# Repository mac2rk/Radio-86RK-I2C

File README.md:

# I2C interface for i8080 (and simlilar) computers

(The wire fixes an error in an intial version of the board; in the Eagle and Gerber files available here the error has been fixed.)

## Introduction

This project is an I2C interface for i8080/i8085/Z80-based computers. The interface is bulit around NXP's PCF8584 I2C bus controller. The PCB is size- and pin-compatible with the i8255 Programmable Peripheral Interface and can be plugged into i8255's socket (of course it requires different code to setup and run). A code example is provided.

## Schematic

[Schematic](Eagle/Radio86RK-I2C-schematic.pdf)

The schematic follows the datasheet for the PCF8584. 

## PCB layout 

[PCB layout](Eagle/Radio86RK-I2C-pcb.pdf)

Note that all parts, with the possible exception of the 4-pin I2C header, are on the underside of the PCB.

## Bill of Materials

U1 (8255) in the schematic is just the DIL male socket, not the actual IC.

Depending on PCF8584 programming, the following oscillator (U4) frequencies can be used: 3, 4.43, 6, 8, 12MHz. With a different board, the clock can of course be shared with the CPU or other preriperals.

Name  | Part               | Value   | Package | Quantity
----- | ------------------ | ------- | ------- | --------
U2    | I2C-bus controller | PCF8584T | S020   | 1
U3    | Signle NAND gate | 741G00DBV | SOT23-5 | 1
U4    | Oscillator         | 12MHz   | 5x7mm   | 1
C1,C2 | Capacitor          | 0.1uF   | 0805    | 2
I2C   | 0.1" pin header    |         | 1x4     | 1

## Example code

Intel 8080 assembler - can be compiled with e.g. [asm8080](https://github.com/mac2rk/asm8080). The code assumes that the PCF8584 I/O ports are mapped to memory addresses 0A000h (data port) and 0A001h (control port). 

    ; PCF8584 use example
    ; 
    ; Define PCF8584 ports
    PCF_BASE    EQU     0A000h
    DATA_REG    EQU     0
    CTRL_REG    EQU     1
    PCF_DATA    EQU     PCF_BASE+DATA_REG
    PCF_CTRL    EQU     PCF_BASE+CTRL_REG
    ;
    ; Define PCF8584 status bit masks
    PCF_BBN     EQU     01h             ; bus busy, active low
    PCF_PIN     EQU     80h             ; pending interrupt, active low
    PCF_LRB     EQU     08h             ; last received bit (typically the ACK bit)
    ;
    ; Define slave address
    SLAVE_ADDR  EQU     8
    ; Byte to send to the slave
    DATA_BYTE   EQU     'A'
    ;
                ORG     0
    ; initialize PCF8584
    PCF_INIT:
    ; program own slave address (this is required even if the address is not used)
                MVI     A, 80h          ; serial interface off; next byte will be loaded into register own address register
                STA     PCF_CTRL
                MVI     A, 55h          ; effective own address becomes 0AAh (55h<<1)
                STA     PCF_DATA
    ; program clock and I2C bus speed
                MVI     A, 0A0h         ; next byte will be loaded into the clock control register S2
                STA     PCF_CTRL
                MVI     A, 1Ch          ; system clock is 12 MHz; SCL = 90 kHz
                STA     PCF_DATA
    ; enable serial interface
                MVI     A, 0C1h         ; enable serial interface, set I2C-bus into idle mode
                STA     PCF_CTRL
    ;
    ; now send something to a slave
    PCF_MASTER_TX:
    ; wait for bus availability
                LDA     PCF_CTRL        ; load status byte
                ANI     PCF_BBN         ; is bus available?
                JZ      PCF_MASTER_TX   ; JIF not available
    ; form the slave address with the R/W bit (R=1, W=0) at LSB
                XRA     A               ; Carry = 0
                MVI     A, SLAVE_ADDR   ; load slave address
                RAL                     ; shift address left, set R/W bit to 0 (write)
                STA     PCF_DATA
    ; generate START condition on the I2C bus and clock out the address byte
                MVI     A, 0C5h          
                STA     PCF_CTRL        ; transmit address + R/W bit
    TX10:
    ; wait for the transmission to finish
                LDA     PCF_CTRL        ; load status byte
                MOV     B, A            ; store status byte to check for acknowledgement later
                ANI     PCF_PIN         ; is transmission complete?
                JNZ     TX10            ; keep polling if not complete
                MOV     A, B
    ; check if the slave acknowledged the address
                ANI     PCF_LRB         ; slave acknowledged?
                JNZ     TXSTOP          ; JIF not acknowledged; maybe the slave is busy or not present at that address
    ; slave acknowledged the address, so send the data
                MVI     A, DATA_BYTE    ; byte to be transferred
                STA     PCF_DATA        ; send the data byte to the slave
    TX20:
    ; wait for the transmission to finish
                LDA     PCF_CTRL        ; load status byte
                ANI     PCF_PIN         ; is transmission complete?
                JNZ     TX20            ; keep polling if not complete
    ; here one can check for acknowledgement and send the next byte, etc.
    TXSTOP:
    ; generate STOP condition on the I2C bus
                MVI     A, 0C3h          
                STA     PCF_CTRL        ; generate STOP condition
    ;
                JMP     PCF_MASTER_TX   ; repeat sending sequence

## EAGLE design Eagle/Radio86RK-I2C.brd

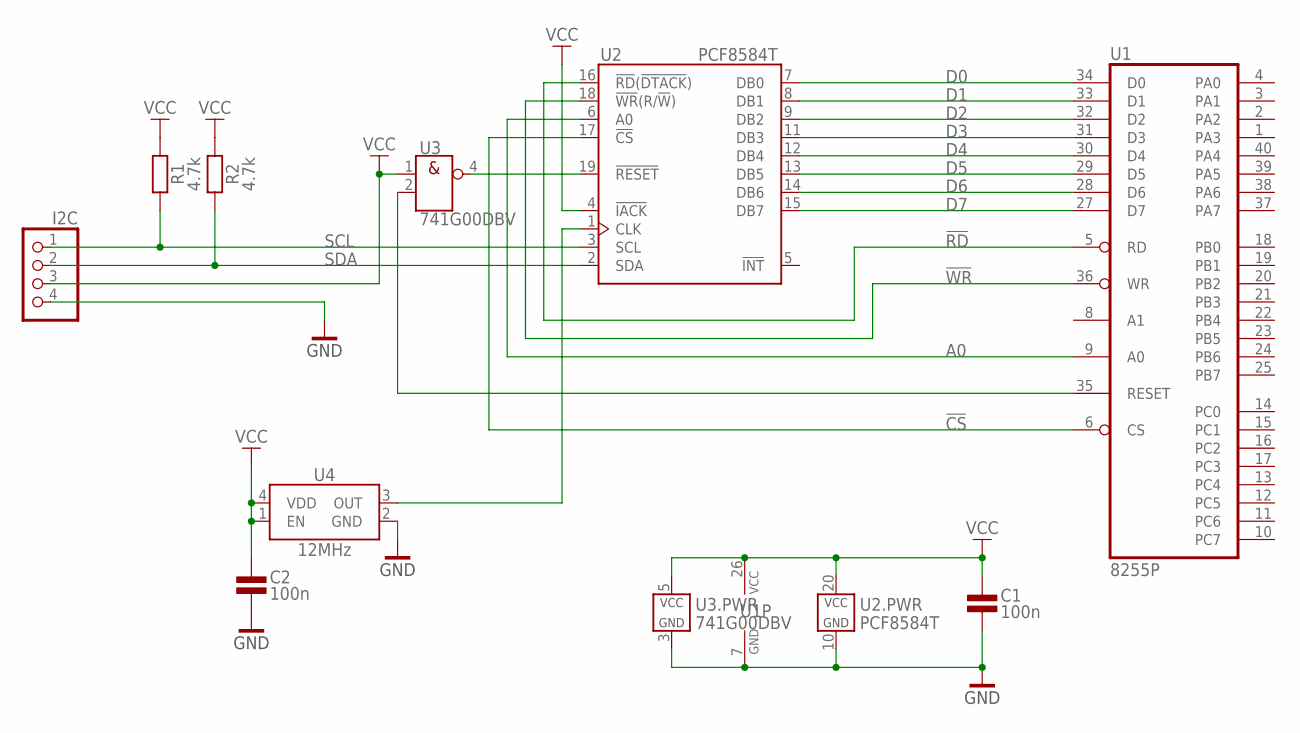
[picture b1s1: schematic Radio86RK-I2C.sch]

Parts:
C1, C2: 100n; 0805@1
I2C: PINHD-1X4; 1X04
R1, R2: 4.7k; 0805
U1: 8255P; DIP40W
U2: PCF8584T; SO20W
U3: 741G00DBV; SOT23-5
U4: 12MHz; XT_5X7

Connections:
!CS: U1.6 (CS), U2.17 (!CS)
!RD: U1.5 (RD), U2.16 (!RD!(!DTACK!))
!WR: U1.36 (WR), U2.18 (!WR!(R/!W!))
A0: U1.9 (A0), U2.6 (A0)
D0: U1.34 (D0), U2.7 (DB0)
D1: U1.33 (D1), U2.8 (DB1)
D2: U1.32 (D2), U2.9 (DB2)
D3: U1.31 (D3), U2.11 (DB3)
D4: U1.30 (D4), U2.12 (DB4)
D5: U1.29 (D5), U2.13 (DB5)
D6: U1.28 (D6), U2.14 (DB6)
D7: U1.27 (D7), U2.15 (DB7)
GND: C1.1, C2.1, I2C.4, U1.7 (GND), U2.10 (GND), U3.3 (GND), U4.2 (GND)
unnamed: U2.19 (!RESET), U3.4 (Y)
unnamed: U2.1 (CLK), U4.3 (OUT)
unnamed: U1.35 (RESET), U3.2 (B)
SCL: I2C.1, R1.1, U2.3 (SCL)
SDA: I2C.2, R2.1, U2.2 (SDA)
VCC: C1.2, C2.2, I2C.3, R1.2, R2.2, U1.26 (VCC), U2.4 (!IACK), U2.20 (VCC), U3.1 (A), U3.5 (VCC), U4.1 (EN), U4.4 (VDD)

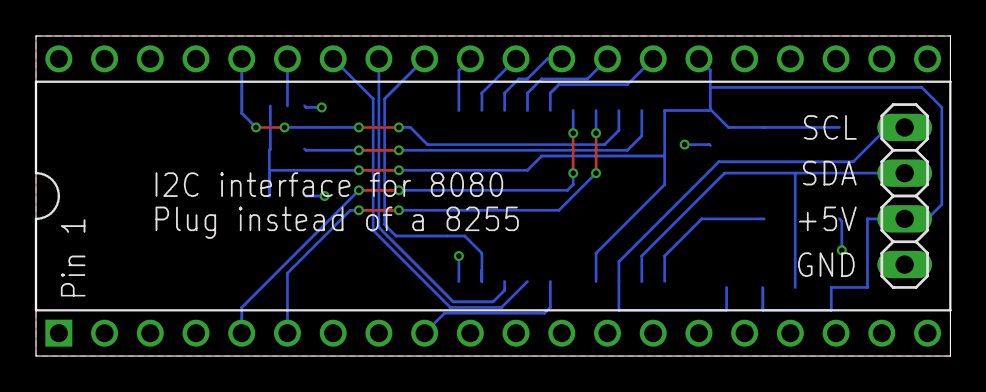
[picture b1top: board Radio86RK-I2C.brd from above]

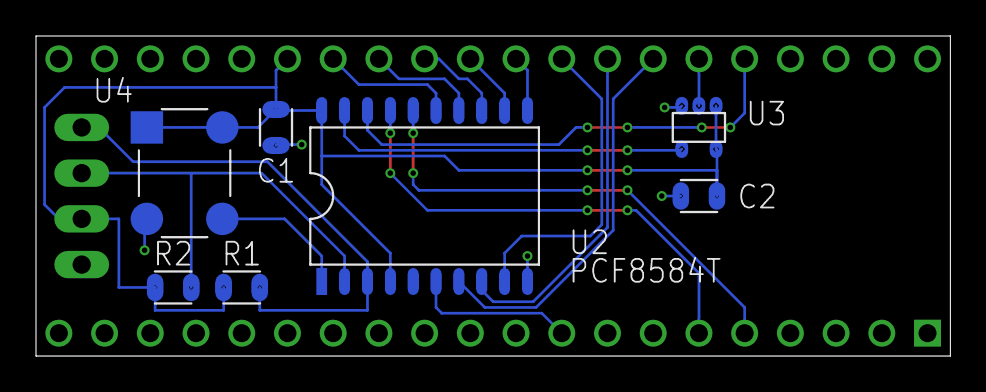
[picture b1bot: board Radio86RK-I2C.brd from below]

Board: 2 copper layers, 50.8 x 17.8 mm, 9 parts (7 on the bottom side), 19 nets.
